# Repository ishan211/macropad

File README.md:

# Ishan's Macropad

This is a Macropad to make my coding/dev flow easier. 

## Features

I added keys to:
- launch wsl
- git commit
- save files
- comment out lines

## BOM
| PCB ID             | Manufacturer Product Name   | Digikey Product Number   | Description                          | Supplier   | Link                                                                                                                                 | Quantity | Cost (CAD) | Cost (USD) |
|:-------------------|:----------------------------|:-------------------------|:-------------------------------------|:-----------|:-------------------------------------------------------------------------------------------------------------------------------------|----------:|:------------|:------------|
| SW1, SW2, SW3, SW4 | MX2A-E1NB                   | 1644-MX2A-E1NB-ND        | Clicky Blue Switch PCB Mounted 5 Pin | Digikey    | https://www.digikey.ca/en/products/detail/cherry-americas-llc/MX2A-E1NB/21738397                                                     |        4 | $10.96     | $7.89       |
| D1, D2             | 4776                        | 1528-4776-ND             | NEOPIXEL RGBW MINI BUTTON PCB -      | Digikey    | https://www.digikey.ca/en/products/detail/adafruit-industries-llc/4776/13550158?s=N4IgTCBcDaIMoGkBsAOAjGABAWQJIDlcBaAURAF0BfIA       |        2 | $15.52     | $11.17      |
| U1                 | 102010428                   | 1597-102010428-ND        | XIAO RP2040                          | Digikey    | https://www.digikey.ca/en/products/detail/seeed-technology-co-ltd/102010428/14672129?s=N4IgTCBcDaIIwFYCcB2AtHADGTWAsYAHGgHIAiIAugL5A |        1 | $6.88      | $4.95       |
| n/a                  |        n/a                      |             n/a             | **Digikey Shipping**                 | Digikey    |                      n/a                                                                                                                 |        1 | $8.00      | $5.76       |
| n/a                  |           n/a                   |          n/a                | **JLCPCB Manufacturing**             | JLCPCB     |                         n/a                                                                                                              |        1 | $2.00      | $1.44       |
| n/a                  |              n/a                |                n/a          | **JLCPCB Shipping**                  | JLCPCB     |                            n/a                                                                                                           |        1 | $22.82     | $16.43      |
| **Total**          |                   n/a           |                     n/a     |     n/a                                 |     n/a       |                           n/a                                                                                                            |      n/a     | **$33.36** | **$24.02**  |

## Images
 
Circuit Schematic Made in KiCAD

PCB Design Made in KiCAD

Case Lid and Base made in Fusion360

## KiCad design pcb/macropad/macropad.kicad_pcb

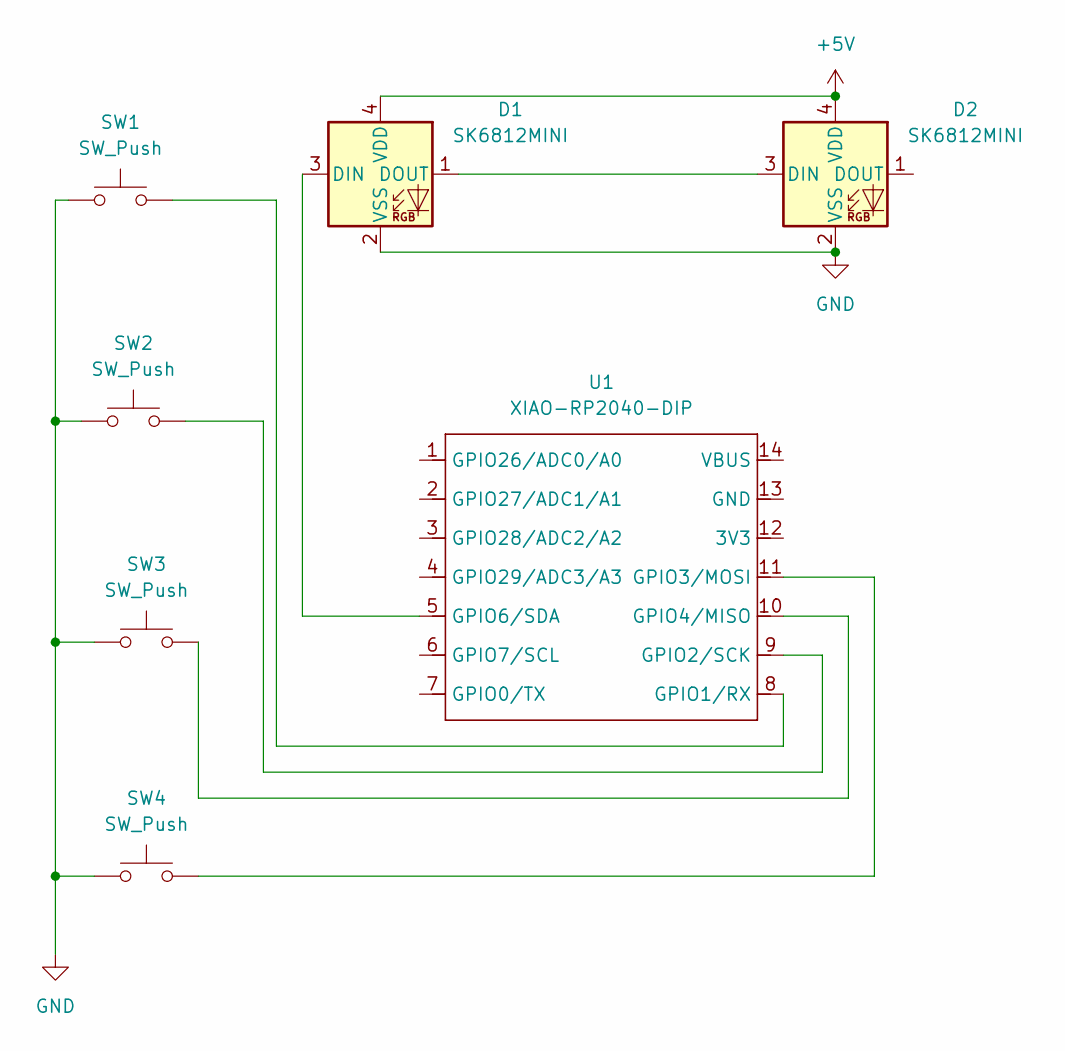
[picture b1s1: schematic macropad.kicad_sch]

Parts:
D1, D2: SK6812MINI; LED_SK6812MINI_PLCC4_3.5x3.5mm_P1.75mm
SW1, SW2, SW3, SW4: SW_Push; SW_Cherry_MX_1.00u_PCB
U1: XIAO-RP2040-DIP

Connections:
+5V: D1.4 (VDD), D2.4 (VDD)
GND: D1.2 (VSS), D2.2 (VSS), SW1.1, SW2.1, SW3.1, SW4.1
unnamed: D1.3 (DIN), U1.5 (GPIO6/SDA)
unnamed: D1.1 (DOUT), D2.3 (DIN)
unnamed: SW1.2, U1.8 (GPIO1/RX)
unnamed: SW2.2, U1.9 (GPIO2/SCK)
unnamed: SW4.2, U1.11 (GPIO3/MOSI)
unnamed: SW3.2, U1.10 (GPIO4/MISO)

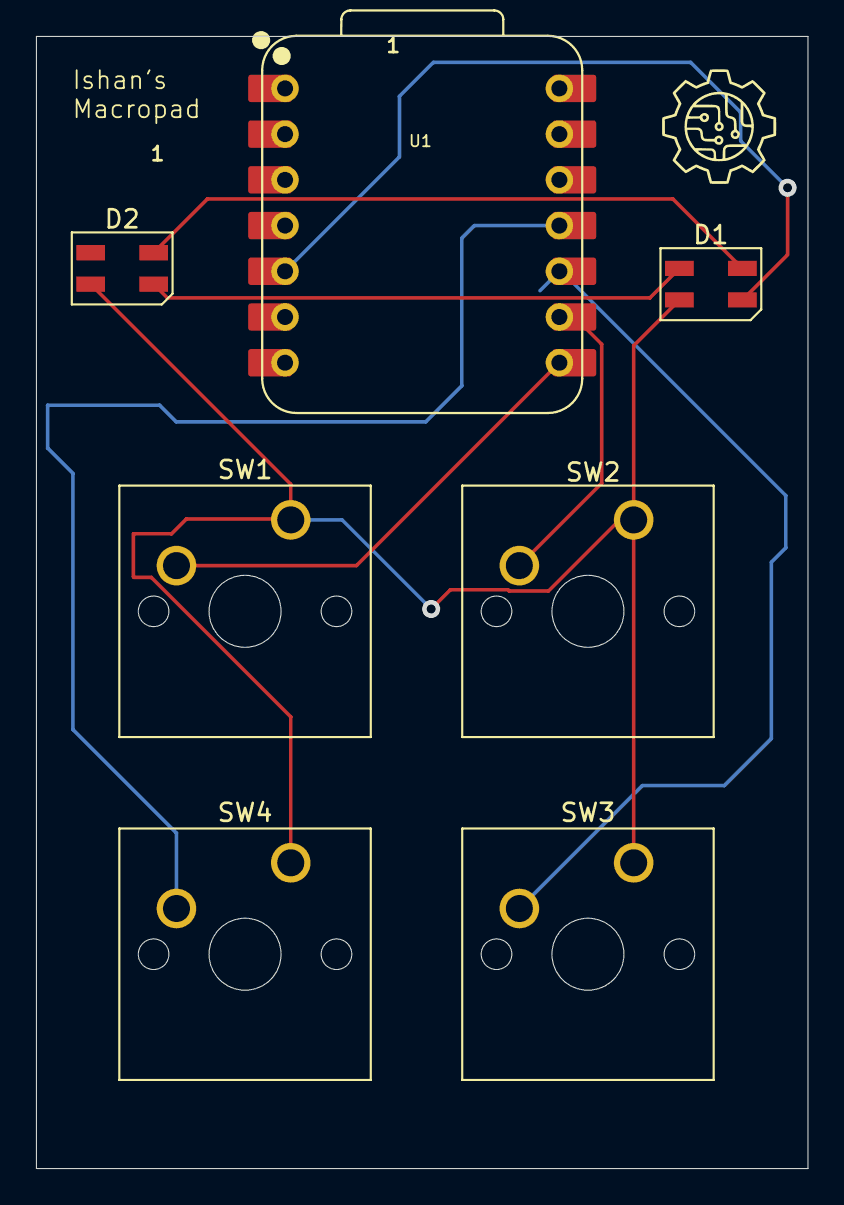
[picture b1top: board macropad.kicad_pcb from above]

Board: 2 copper layers, 42.9 x 62.9 mm, 7 parts (0 on the bottom side), 8 nets.

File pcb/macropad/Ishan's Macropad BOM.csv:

PCB ID,Manufacturer Product Name,Digikey Product Number,Description,Supplier,Link ,Quantity,Cost (CAD),Cost (USD)
"SW1, SW2, SW3, SW4",MX2A-E1NB,1644-MX2A-E1NB-ND,Clicky Blue Switch PCB Mounted 5 Pin,Digikey,https://www.digikey.ca/en/products/detail/cherry-americas-ll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,4,$10.96,$7.89
"D1, D2",4776,1528-4776-ND,NEOPIXEL RGBW MINI BUTTON PCB -,Digikey,https://www.digikey.ca/en/products/detail/adafruit-industrie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,2,$15.52,$11.17
U1,102010428,1597-102010428-ND,XIAO RP2040,Digikey,https://www.digikey.ca/en/products/detail/seeed-technology-c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,1,$6.88,$4.95
n/a,n/a,n/a,Digikey Shipping,Digikey,n/a,1,$8.00,$5.76
n/a,n/a,n/a,JLCPCB Manufacturing,JLCPCB,n/a,1,$2.00,$1.44
n/a,n/a,n/a,JLCPCB Shipping,JLCPCB,n/a,1,$22.82,$16.43
Total,n/a,n/a,n/a,n/a,n/a,n/a,$33.36,$24.02

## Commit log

2025-05-21 Added Project Files
